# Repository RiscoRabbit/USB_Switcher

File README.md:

# USB HID Switcher

高度なUSB HID切り替え装置です。二個のRaspberry Pi Picoを使用して、複数のPCを切り替えながらUSB Keyboardやマウス操作ができます。
Advanced USB HID switching device. Uses two Raspberry Pi Picos to enable USB keyboard and mouse operation while switching between multiple PCs.

## 使い方

### 配線

二台のRP2350-USB-Aを下記の通り接続します

### 初期セットアップ

#### 1. ファームウェアの書き込み

1. **BOOTSELモード**でPicoをPCに接続します
   - BOOTSELボタンを押しながらUSBケーブルを接続
   - PicoがRPI-RP2ドライブとして認識されます

2. **ファームウェアファイルのコピー**
   ```bash
   # ビルドしたuf2ファイルをPicoにコピー
   cp build/usb_hid_switcher/usb_hid_switcher.uf2 /media/RPI-RP2/
   ```
   
3. **自動再起動**
   - ファイルコピー完了後、Picoが自動的に再起動します
   - USB HID SwitcherとしてPCに認識されます

#### 2. 切り替え操作

以下のキー操作でPC間の切り替えが可能です：

- **CapsLock + M**: PC1（SWITCH 0）に切り替え
- **CapsLock + N**: PC2（SWITCH 1）に切り替え

## 主な機能

### 🔄 **デュアルUSBモード**
- **USB Host**: 複数のUSB HIDデバイスを同時接続、USB Hubの使用も可能
- **USB Device**: キーボード、マウス、ゲームパッドとしてPCに認識

### 🎮 **対応デバイス**
- **キーボード**: BOOTプロトコル、REPORTプロトコル対応
- **マウス**: 16bit高精度、ホイール・パン操作対応

### 📡 **通信インターフェース**
- **CDC (Virtual COM Port)**: USB経由でPCから仮想COMポートとして認識され、設定やコマンド送信が可能
- **UART0**: デバッグ出力
- **UART1**: Pico間通信
- **File System**: LittleFSによる設定・スクリプト保存

### 🔧 **高度な機能**
- デバイス別プロファイル設定
- メタキー機能（キー組み合わせの動的変更）

## ハードウェア構成

### ピン配置

#### Pico2 (RP2350)
```
GPIO 12-13 : USB Host (D+/D-)
GPIO 16    : WS2812 RGB LED
GPIO 4-5   : UART1
GPIO 0-1   : UART0 (デバッグ/通信)
GPIO 26    : I2C1 SDA (OLED Display)
GPIO 27    : I2C1 SCL (OLED Display)
```

## ビルド方法

### 1. 依存関係
```bash
# Pico SDK (v1.5.0以降推奨)
export PICO_SDK_PATH=/path/to/pico-sdk

# 必要なツール
sudo apt install cmake gcc-arm-none-eabi build-essential
```

### 2. ビルド手順
```bash
# プロジェクトディレクトリに移動
cd USB_Switcher
mkdir build && cd build
cmake .. -DPICO_BOARD=pico2 -DPICO_SDK_PATH=$PICO_SDK_PATH
# ビルド実行
make
```

### 3. ファームウェア書き込み
```bash
# BOOTSELモードでPicoを接続後
cp usb_switcher/usb_switcher.uf2 /media/RPI-RP2/
```

## LED状態表示

| 色 | 状態 |
|---|---|
| 🟡 黄 | 別Picoへ信号転送中（UART経由出力） |
| 🟢 緑 | アクティブ |
| 点滅 | アクティブ状態（入力処理中） |

## 対応デバイス例

### マウス
- Logicool G300s (046d:c246)
- Logicool Unified Receiver (046d:c52b)
- 各種ゲーミングマウス

### キーボード
- 標準USBキーボード

## ライセンス

このプロジェクトはMITライセンスです。各コンポーネントのライセンスは各コンポーネントのライセンスファイルを参照してください。

## コントリビューション

バグ報告や機能提案はIssueでお願いします。プルリクエストも歓迎します。

## 関連リンク

- [Pico-PIO-USB](https://github.com/sekigon-gonnoc/Pico-PIO-USB)
- [Raspberry Pi Pico SDK](https://github.com/raspberrypi/pico-sdk)
- [TinyUSB](https://github.com/hathach/tinyusb)
- [FreeRTOS](https://www.freertos.org/)
- [LittleFS](https://github.com/littlefs-project/littlefs)
- [Lua](https://www.lua.org/)

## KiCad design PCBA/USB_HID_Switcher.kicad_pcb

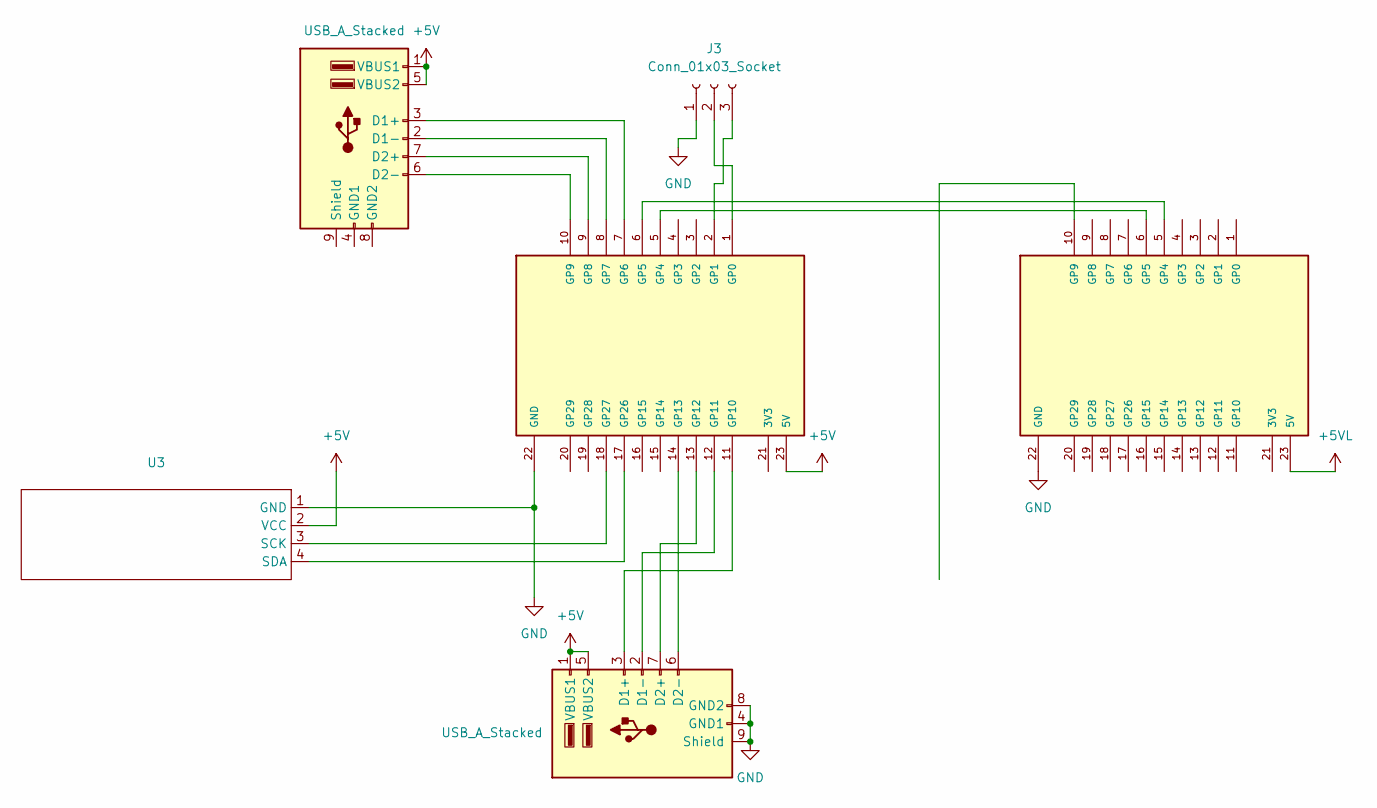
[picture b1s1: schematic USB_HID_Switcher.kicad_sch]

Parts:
J1, J2: USB_A_Stacked; USB_A_CUI_UJ2-ADH-TH_Horizontal_Stacked
J3: Conn_01x03_Socket; PinHeader_1x03_P2.54mm_Vertical
U1, U2: RP2040-ZERO; MODULE_RP2040-ZERO; PARTREV NA
U3: OLED128x32

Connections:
+5V: J1.1 (VBUS1), J1.5 (VBUS2), J2.1 (VBUS1), J2.5 (VBUS2), U1.23 (5V), U3.2 (VCC)
+5VL: U2.23 (5V)
GND: J1.4 (GND1), J1.8 (GND2), J1.9 (Shield), J3.1, U1.22 (GND), U2.22 (GND), U3.1 (GND)
unnamed: J1.3 (D1+), U1.11 (GP10)
unnamed: J1.2 (D1-), U1.12 (GP11)
unnamed: J1.7 (D2+), U1.13 (GP12)
unnamed: J1.6 (D2-), U1.14 (GP13)
unnamed: J2.3 (D1+), U1.7 (GP6)
unnamed: J2.2 (D1-), U1.8 (GP7)
unnamed: J2.7 (D2+), U1.9 (GP8)
unnamed: J2.6 (D2-), U1.10 (GP9)
unnamed: J3.2, U1.1 (GP0)
unnamed: J3.3, U1.2 (GP1)
unnamed: U1.5 (GP4), U2.6 (GP5)
unnamed: U1.6 (GP5), U2.5 (GP4)
unnamed: U1.17 (GP26), U3.4 (SDA)
unnamed: U1.18 (GP27), U3.3 (SCK)

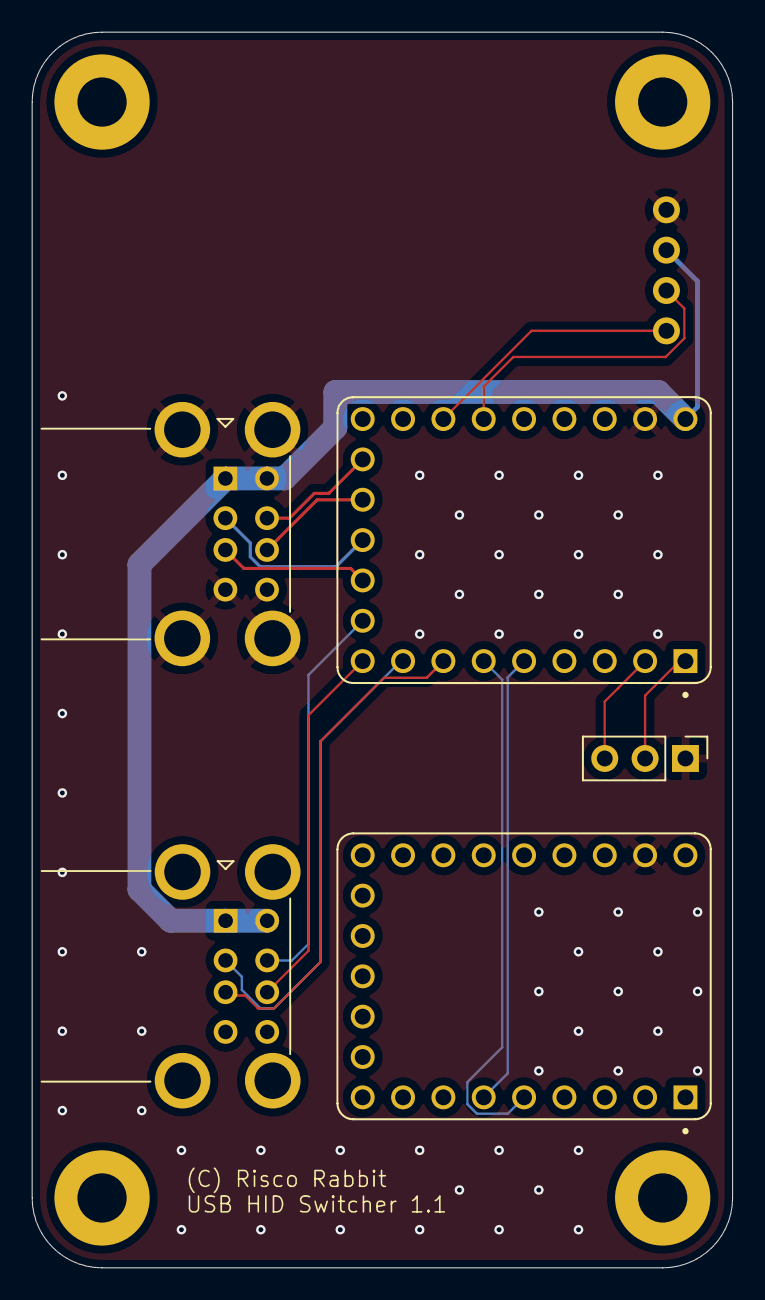
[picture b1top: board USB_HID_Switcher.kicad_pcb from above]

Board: 2 copper layers, 44.1 x 77.8 mm, 6 parts (0 on the bottom side), 16 nets.

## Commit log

2025-10-31 Initial commit: USB Switcher project
2025-10-31 Initial release
2025-10-31 Readmeをupdateしました。
